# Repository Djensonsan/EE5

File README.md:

# Smart Mowing Machine Project

The goal of this project was to design a "smart lawn mower" for a company named A.W.B Schots N.V..

This project included the design of custom PCBs to be placed on an industrial lawn mower. These PCBs were connected with arduino modules that communicated over a bus protocol. One master arduino module was resposible for storing data and pushing data to the operator's phone. The data was then pushed to the cloud (Microsoft Azure) and visualised using Power BI. The gathered data was used to help the company analyse the operator's efficiency and help the company save money by characterizing the difficulty of different lawn mowing routes.

This GitHub repository holds all Arduino resources used for this Project.
The code for the Android application is kept in a different repository here:
https://github.com/NathanHerrebosch/AWB_App.git

Please also note the Documents folder where additional documentation can be found for testing/implementing our project.

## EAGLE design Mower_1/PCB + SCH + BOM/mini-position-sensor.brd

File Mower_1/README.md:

# Mower 1

This project implements smart sensors and data visualization for an industrial type lawnmower. 

## Compilation

All files with the “.ino” extension, can be compiled using the Arduino IDE. 
Please note that some code is run on an Arduino Mega while other parts are run on Arduino Uno, when compiling please select the correct board!
There is no need to upload the code to the Arduino’s in a certain order.

## Libraries

A libraries folder is included that holds al used libraries. For more information on how to include libraries, please visit: https://www.arduino.cc/en/hacking/libraries

## GitHub
There are 2 GitHub pages, one for the Arduino Code and one for the Android code:
https://github.com/Djensonsan/EE5
https://github.com/NathanHerrebosch/AWBApp

The latest and older versions of the code can be found here. 

## Manual & Installation guide
For more information, read our manual and installation guide. They are also included in the ZIP-file. 

## Video of the final result
https://kuleuven.mediaspace.kaltura.com/media/final_video_lastversion/1_84033um8

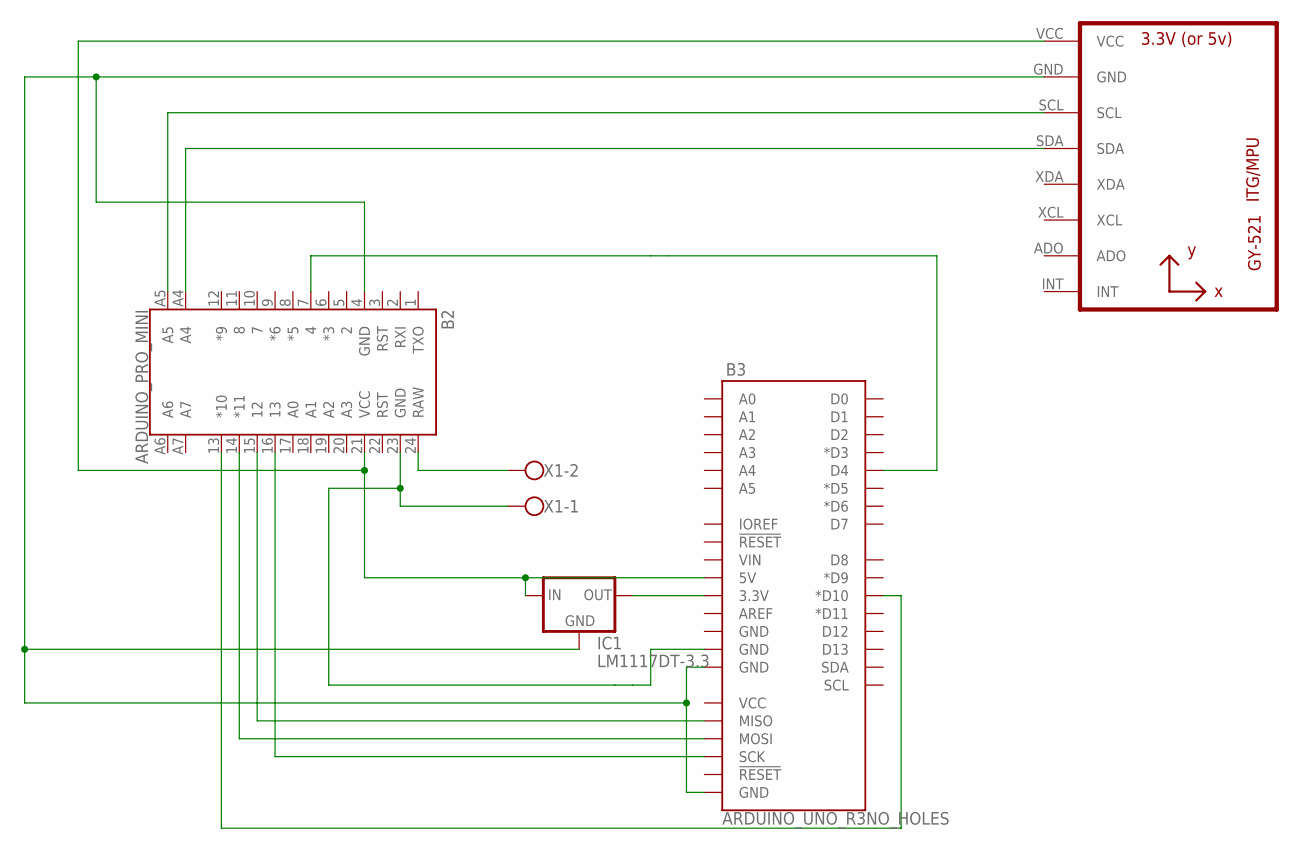
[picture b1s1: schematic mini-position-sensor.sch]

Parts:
B2: ARDUINO_PRO_MINI
B3: ARDUINO_UNO_R3NO_HOLES; ARDUINO_R3_NO_HOLES
IC1: LM1117DT-3.3; TO252
U1: GY-521MPU6050; GY-521
X1: W237-102

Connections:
unnamed: B2.7 (4), B3.D4
unnamed: B2.4 (GND), B3.GND@1 (GND), B3.GND@2 (GND), IC1.1 (GND), U1.GND
unnamed: B2.14 (*11), B3.MOSI
unnamed: B2.15 (12), B3.MISO
unnamed: B2.A4, U1.SDA
unnamed: B2.A5, U1.SCL
unnamed: B3.3.3V, IC1.3 (OUT)
unnamed: B2.24 (RAW), X1.2
unnamed: B2.16 (13), B3.SCK
unnamed: B2.13 (*10), B3.D10 (*D10)
unnamed: B2.23 (GND), B3.GND@3 (GND), X1.1
unnamed: B2.21 (VCC), B3.5V, IC1.2 (IN), U1.VCC

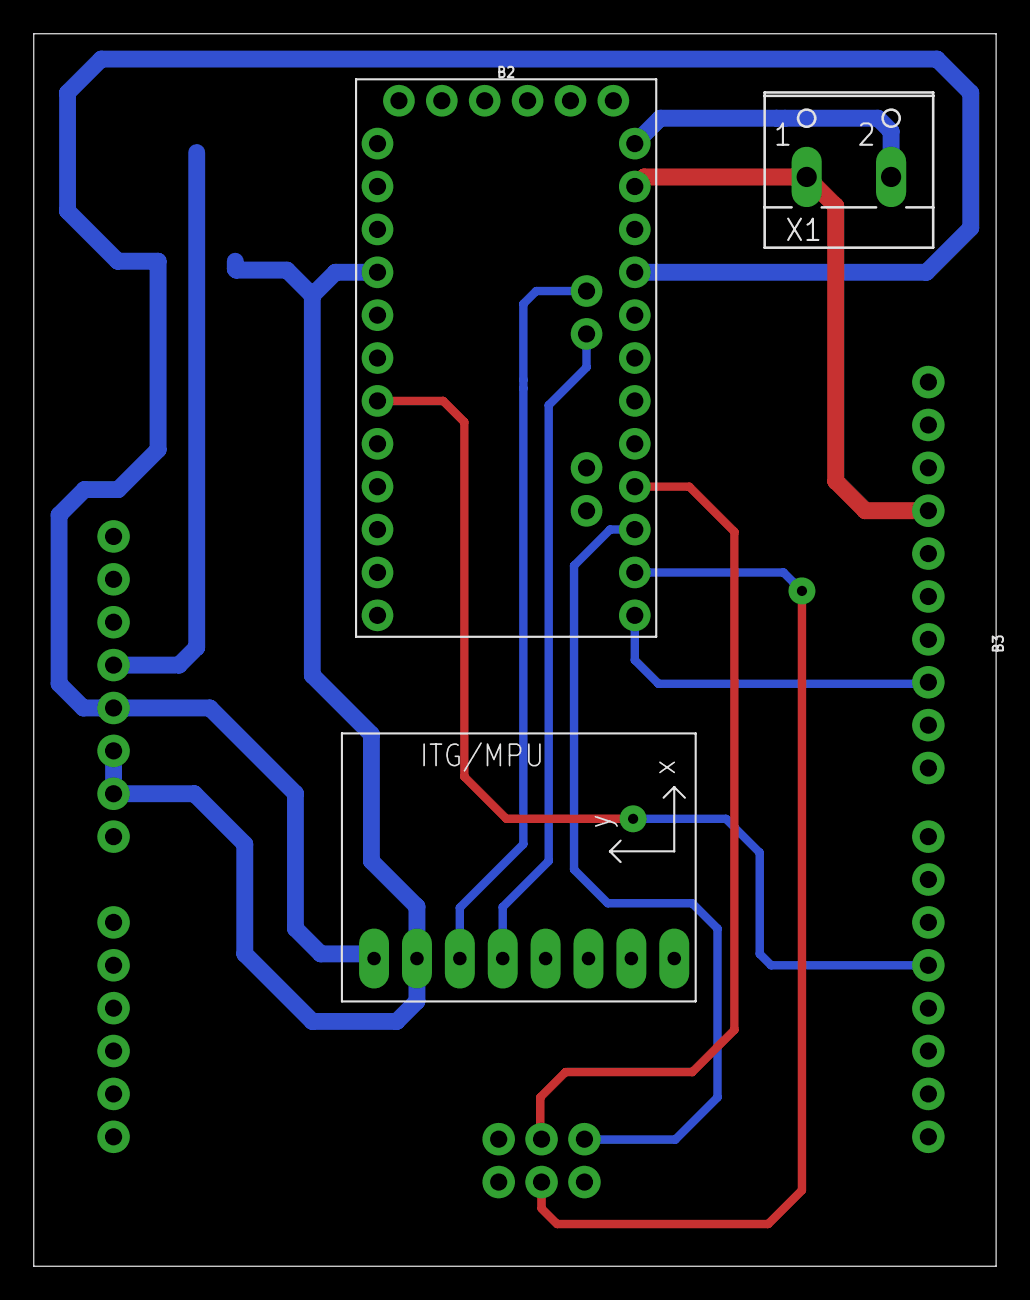
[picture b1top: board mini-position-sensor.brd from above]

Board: 2 copper layers, 57.0 x 73.0 mm, 5 parts (1 on the bottom side), 12 nets.

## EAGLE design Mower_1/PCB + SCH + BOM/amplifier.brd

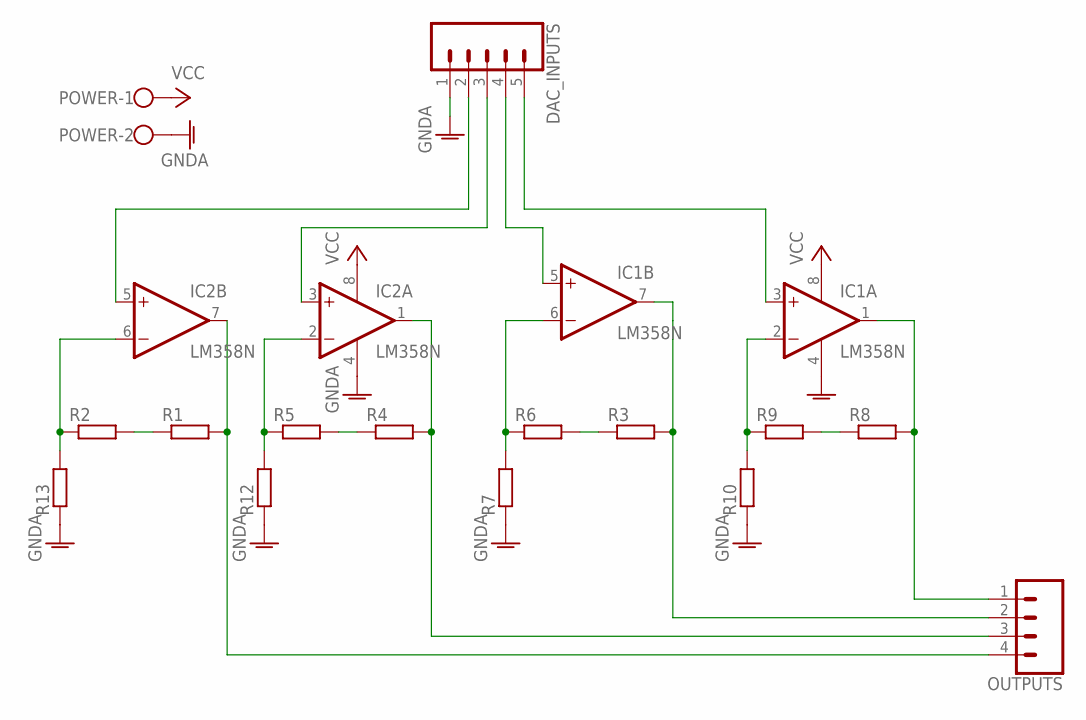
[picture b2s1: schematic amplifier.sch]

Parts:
DAC_INPUTS: CONN_05; 1X05
IC1, IC2: LM358N; DIL08
OUTPUTS: CONN_04; 1X04
POWER: W237-102
R1, R2, R3, R4, R5, R6, R7, R8, R9, R10, R12, R13: R-EU_0204/7; 0204/7

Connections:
GNDA: DAC_INPUTS.1, IC1.4 (V-), IC2.4 (V-), POWER.2, R7.1, R10.1, R12.1, R13.1
unnamed: DAC_INPUTS.5, IC1.3 (+IN)
unnamed: DAC_INPUTS.3, IC2.3 (+IN)
unnamed: DAC_INPUTS.4, IC1.5 (+IN)
unnamed: DAC_INPUTS.2, IC2.5 (+IN)
unnamed: IC2.1 (OUT), OUTPUTS.3, R4.2
unnamed: IC2.2 (-IN), R5.1, R12.2
unnamed: R4.1, R5.2
unnamed: IC2.7 (OUT), OUTPUTS.4, R1.2
unnamed: R1.1, R2.2
unnamed: IC2.6 (-IN), R2.1, R13.2
unnamed: R3.1, R6.2
unnamed: IC1.6 (-IN), R6.1, R7.2
unnamed: IC1.7 (OUT), OUTPUTS.2, R3.2
unnamed: R8.1, R9.2
unnamed: IC1.2 (-IN), R9.1, R10.2
unnamed: IC1.1 (OUT), OUTPUTS.1, R8.2
VCC: IC1.8 (V+), IC2.8 (V+), POWER.1

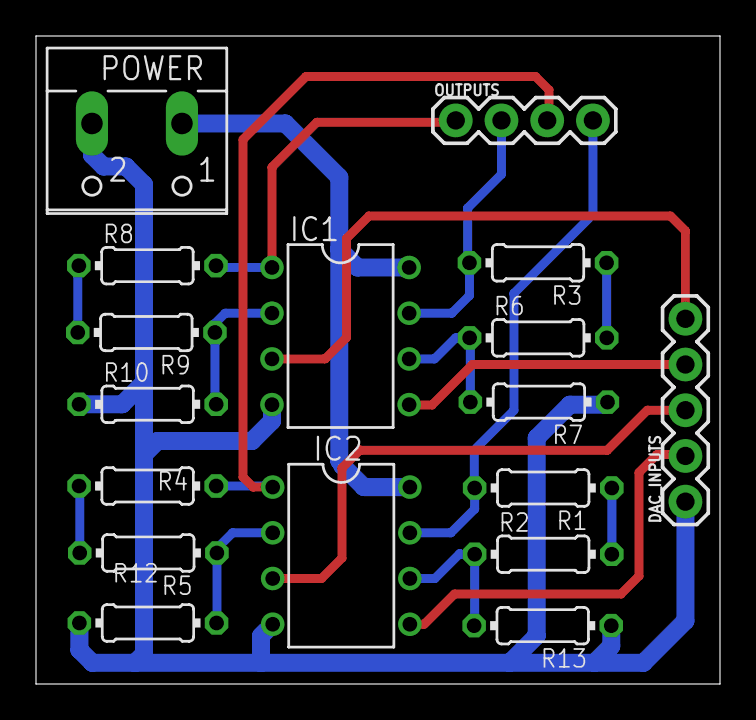
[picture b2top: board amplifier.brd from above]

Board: 2 copper layers, 38.0 x 36.0 mm, 17 parts (0 on the bottom side), 18 nets.

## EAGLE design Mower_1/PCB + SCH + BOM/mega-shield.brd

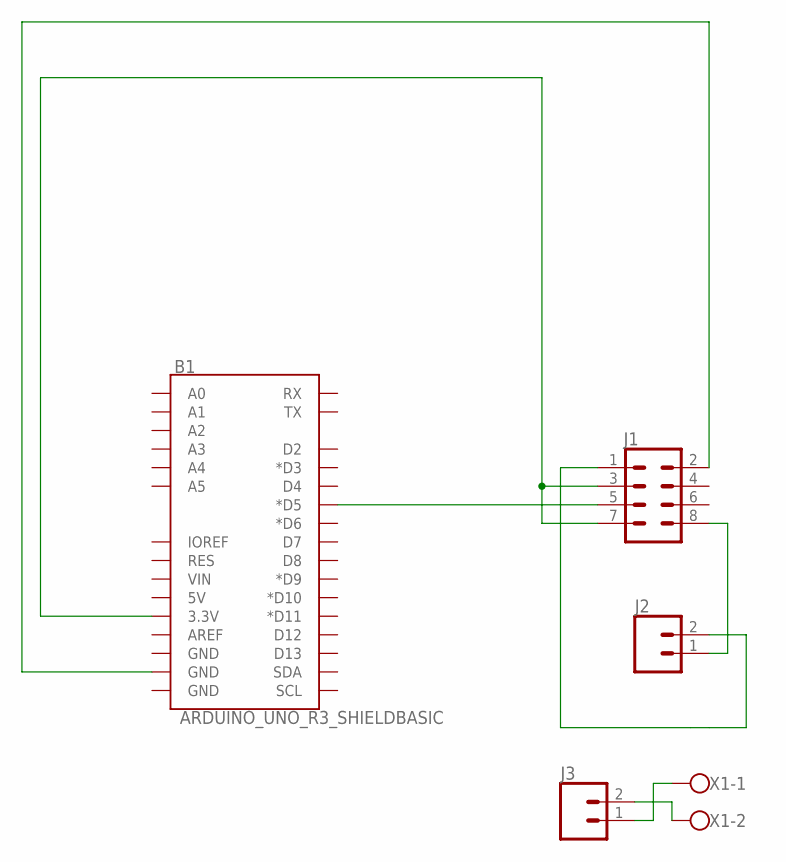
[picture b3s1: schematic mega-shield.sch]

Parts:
B1: ARDUINO_UNO_R3_SHIELDBASIC; UNO_R3_SHIELD
J1: CONN_04X2; 2X4
J2, J3: CONN_02; 1X02
X1: W237-102

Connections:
unnamed: B1.3.3V, J1.3, J1.7
unnamed: J1.8, J2.1
unnamed: B1.D5 (*D5), J1.5
unnamed: J1.1, J2.2
unnamed: J3.1, X1.1
unnamed: B1.GND@1 (GND), J1.2
unnamed: J3.2, X1.2

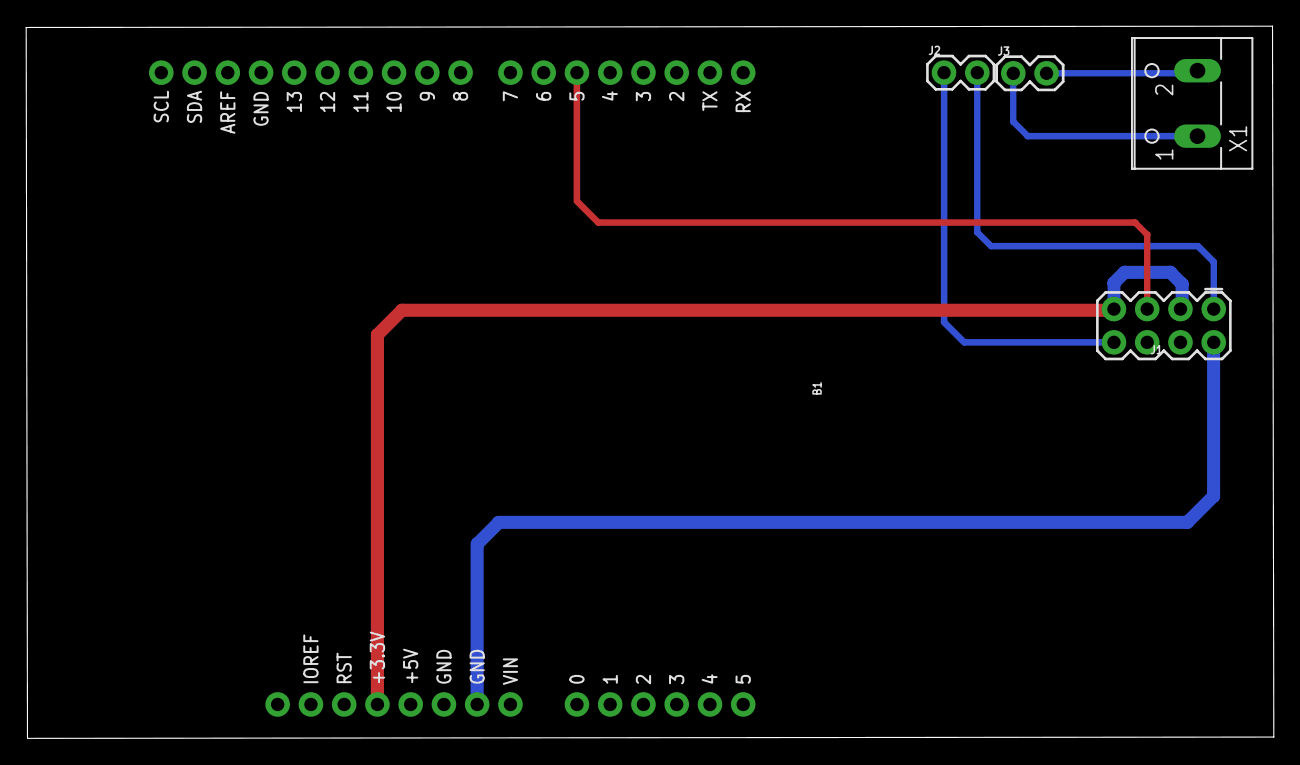
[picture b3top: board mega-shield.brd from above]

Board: 2 copper layers, 95.3 x 54.4 mm, 5 parts (0 on the bottom side), 7 nets.

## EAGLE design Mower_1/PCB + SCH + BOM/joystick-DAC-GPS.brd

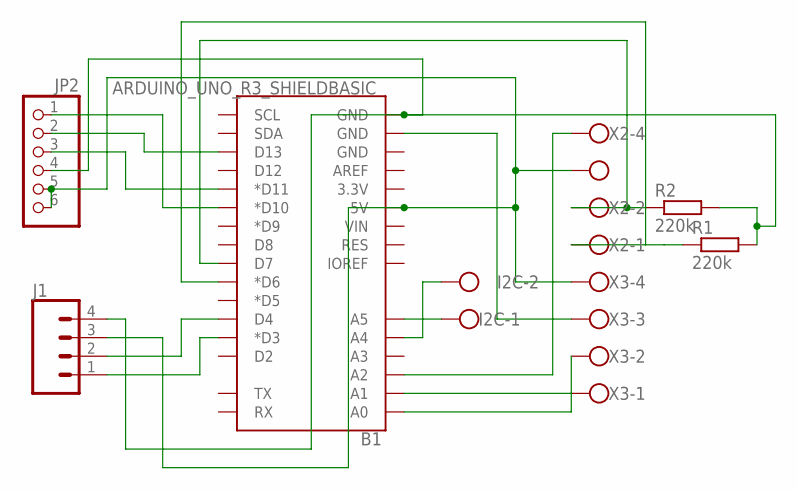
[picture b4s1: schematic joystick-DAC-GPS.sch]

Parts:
B1: ARDUINO_UNO_R3_SHIELDBASIC; UNO_R3_SHIELD
I2C: W237-102
J1: CONN_04; 1X04
JP2: PINHD-1X6; 1X06
R1, R2: 220k; 0204/7
X2, X3: W237-4

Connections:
unnamed: B1.5V, J1.3, JP2.5, JP2.6, X2.3, X3.4
unnamed: B1.A0, X3.2
unnamed: B1.A1, X3.1
unnamed: B1.GND@1 (GND), X3.3
unnamed: B1.GND@0 (GND), J1.4, JP2.4, R1.2, R2.2
unnamed: B1.A4, I2C.2
unnamed: B1.A5, I2C.1
unnamed: B1.A2, X2.4
unnamed: B1.D10 (*D10), JP2.1
unnamed: B1.D7, R2.1, X2.2
unnamed: B1.D11 (*D11), JP2.3
unnamed: B1.D13, JP2.2
unnamed: B1.D6 (*D6), R1.1, X2.1
unnamed: B1.D3 (*D3), J1.1
unnamed: B1.D4, J1.2

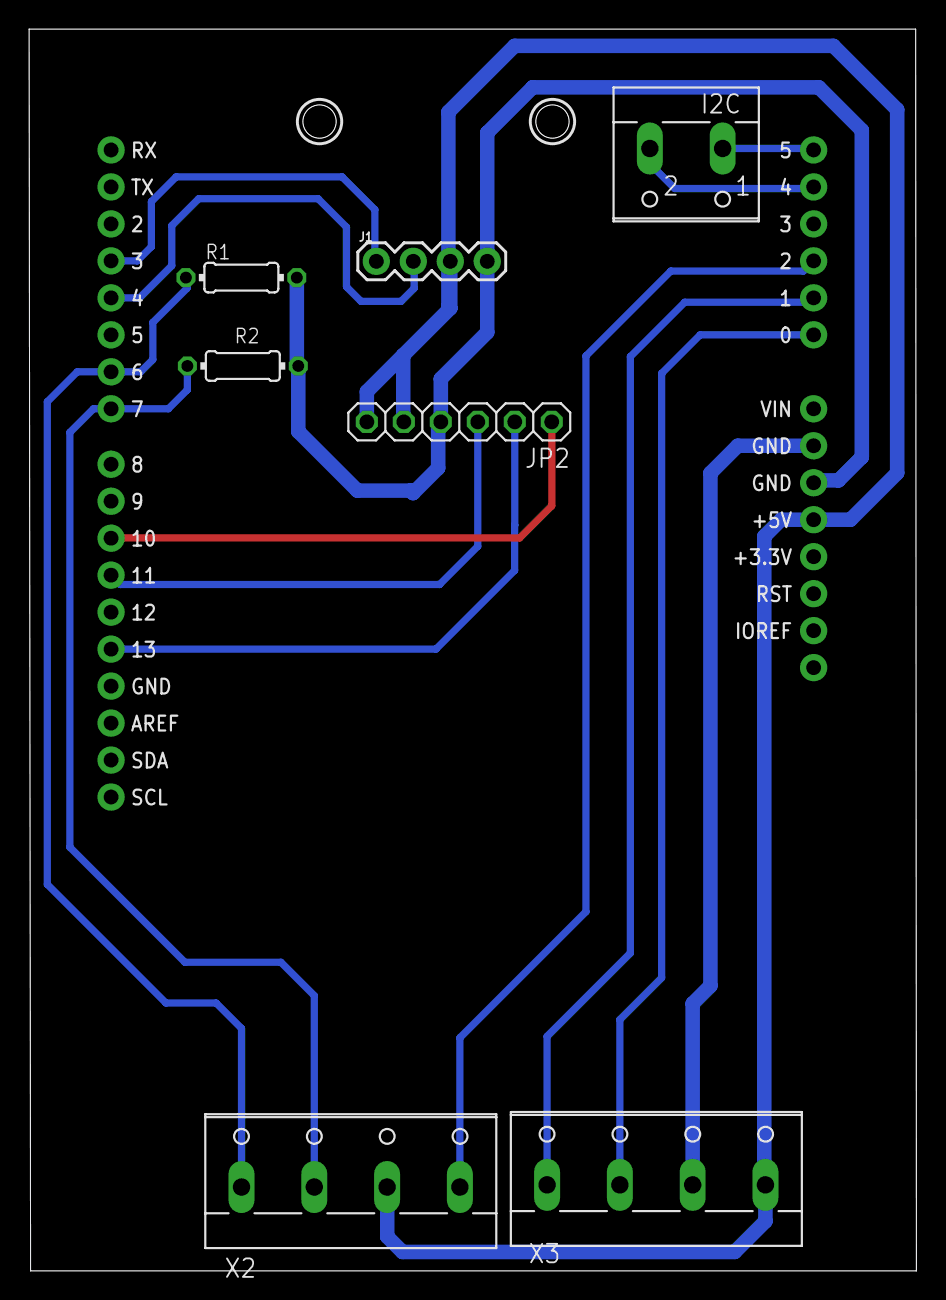
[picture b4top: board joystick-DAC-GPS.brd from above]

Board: 2 copper layers, 60.9 x 85.3 mm, 8 parts (0 on the bottom side), 15 nets.

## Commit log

2019-04-03 Create Arduino Joystick
2019-04-03 Rename Arduino_GPS to Test_Arduino_GPS
2019-04-03 Create Test_GPS
2019-04-03 Rename Mega_Test to Test_Master
2019-04-03 Rename CAN Bus receiver to Test_CANBusReceiver
2019-04-03 Rename angle_measurement to Test_Angle_Measurement
2019-04-03 Rename Test_CANBusReceiver to Test_CAN_Receiver
2019-04-03 Rename Arduino_webserver to Test_Arduino_AP
2019-04-03 Rename temperature_test to Test_Temperature
2019-04-03 Rename temperature_controlled_motor to Test_Temperature_Controlled_Motor
2019-04-03 Rename Ventilator_code.ino to Test_Motor.ino
2019-04-03 Rename timer_test to Test_Timer
2019-04-03 Rename Master_Sensor_Controlled_Motor to Arduino_Ventilator
2019-04-03 Rename Master_Arduino to Arduino_Master
2019-04-03 Rename Arduino Joystick to Arduino_Joystick
2019-04-03 Rename arduino_mini_code_V1 to Test_Position_Sensor
2019-04-03 Rename Position_sensor to Test_Position_Sensor_2
2019-04-03 Rename Arduino_Position_Sensor.ino to Arduino_Position_Sensor
2019-04-03 Rename Arduino_Position_Sensor to Arduino_Position_Sensor.ino
2019-04-03 Update Test_CAN_Receiver
2019-04-04 Update Test_Master
2019-04-04 Update Arduino_Master
2019-04-04 Rename Arduino_Master to Arduino_Master.ino
2019-04-15 Create positionSensor_kalmanFilter
    Implemented both Kalman filter and complementary filter and compare both results.
    The library of the Kalman filter can be downloaded in the following page:
    https://github.com/TKJElectronics/KalmanFilter
2019-04-26 Create Arduino_Position_Sensor_V2
    The latest version up to 4/26/2019
    New features:
    1) User-defined filter by setting MODE to be 0(Kalman) or 1(Complementary)
    2) Implemented a circular buffer and averaging the raw value from MPU to get rid of the vibration effect
2019-04-26 The latest version of Position sensor up to 4/26
    The latest version up to 4/26/2019
    New features:
    1) User-defined filter by setting MODE to be 0(Kalman) or 1(Complementary)
    2) Implemented a circular buffer and averaging the raw value from MPU to get rid of the vibration effect
2019-04-26 The latest version up to 4/26/2019
2019-05-02 Create refactored_master
2019-05-06 Update Arduino_Joystick
2019-05-10 Create Test_joystic_2
2019-05-10 Create Test_Master_2
2019-05-20 The latest version
2019-05-20 The first version
2019-05-21 Create h
2019-05-21 Create Video_Link
2019-05-22 The latest version upto 5/22/2019
    The latest version upto 5/22/2019
2019-05-23 The latest version upto 5/23/2019
    The latest version upto 5/23/2019

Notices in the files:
parts and their libraries:
SparkFun-Connectors: Licensing: Creative Commons ShareAlike 4.0 International - https://creativecommons.org/licenses/by-sa/4.0
